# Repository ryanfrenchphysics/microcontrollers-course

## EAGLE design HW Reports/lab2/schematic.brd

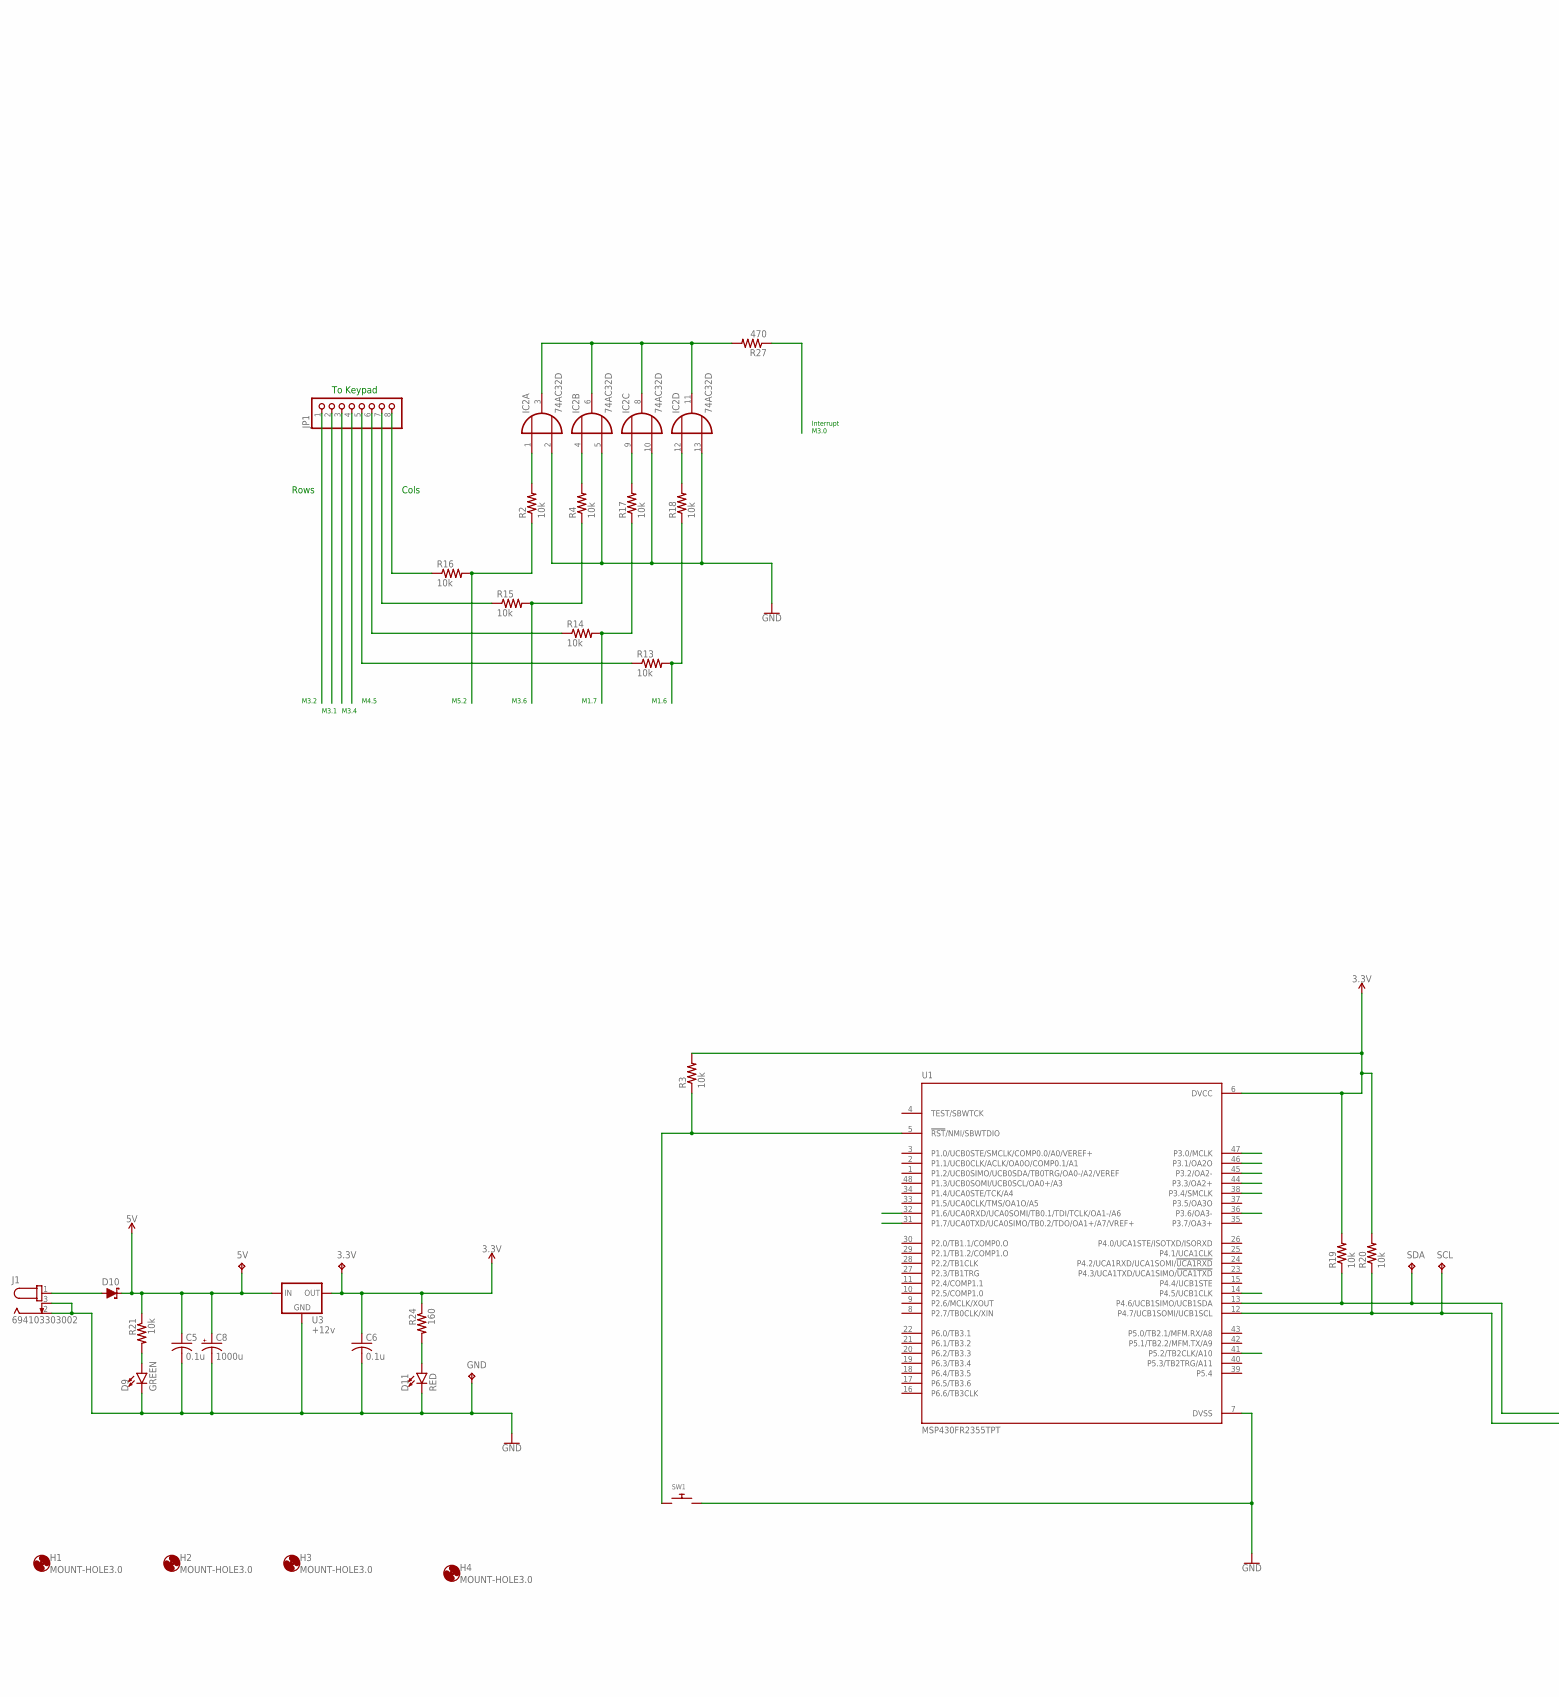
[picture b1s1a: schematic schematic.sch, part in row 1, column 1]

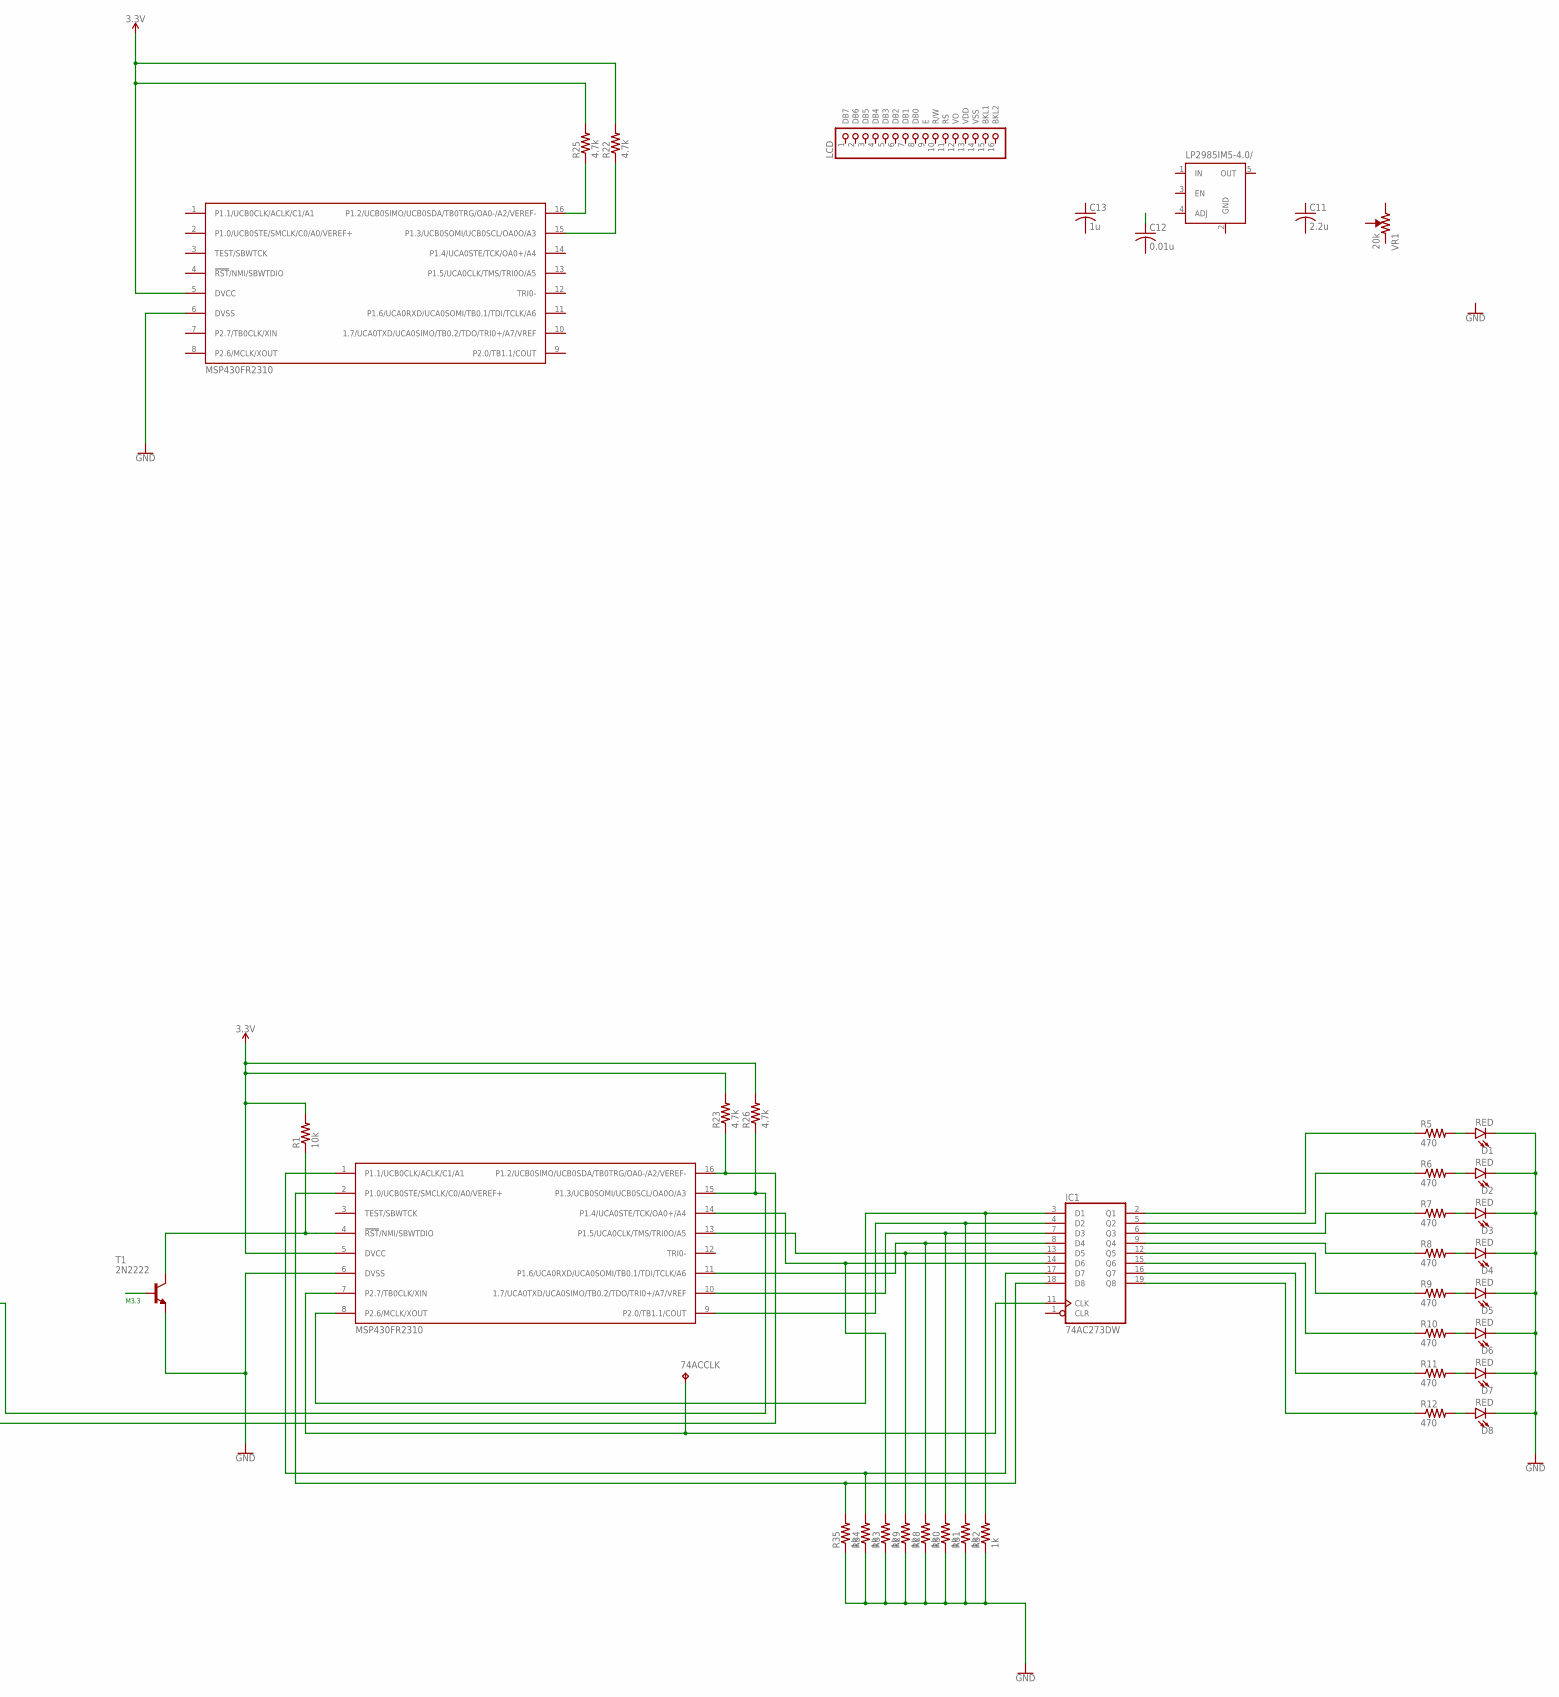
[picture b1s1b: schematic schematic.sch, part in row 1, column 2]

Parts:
3.3V, 5V, 74ACCLK: TPPAD1-17; P1-17
C5, C6: 0.1u; C1206
C8: 1000u; E2,5-6E
C11: 2.2u; C0603
C12: 0.01u; C0603
C13: 1u; C0603
D1, D2, D3, D4, D5, D6, D7, D8, D11: RED; LED-1206
D9: GREEN; LED-1206
D10: DIODE-SCHOTTKY-SS14; SMA-DIODE
GND: TPPAD1-17; P1-17
H1, H2, H3, H4: MOUNT-HOLE3.0; 3,0
IC1: 74AC273DW; SO20W
IC2: 74AC32D; SO14
J1: 694103303002
JP1: PINHD-1X8/90; 1X08/90
LCD: PINHD-1X16; 1X16
LP2985IM5-4.0/: LP2985IM5-4.0/; SOT23-5
R1: 10k; RESC1608X60
R2, R3, R4, R13, R14, R15, R16, R17, R18, R19, R20, R21: 10k; RESC3216X70
R5, R6, R7, R8, R9, R10, R11, R12, R27: 470; RESC3216X70
R22, R23, R25, R26: 4.7k; RESC1608X60
R24: 160; RESC3216X70
R28, R29, R30, R31, R32, R33, R34, R35: 1k; RESC3216X70
SCL: TPPAD1-17; P1-17
SDA: TPPAD1-17; P1-17
SW1: SWITCH_PUSHBUTTONC&K_KSS; BTN_CK_KSS
T1: 2N2222; TO92-EBC-OVAL
U1: MSP430FR2355TPT; QFP50P900X900X160-48N
U3: +12v; TO-252
U$1, U$2: MSP430FR2310; SOP65P640X120-16N
VR1: 20k; TRIMPOT-SMD-3MM-CLOSED

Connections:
5V: 5V.TP, C5.1, C8.+, D10.C, R21.1, U3.1 (IN)
GND: C5.2, C6.2, C8.-, D1.C, D2.C, D3.C, D4.C, D5.C, D6.C, D7.C, D8.C, D9.C, D11.C, GND.TP, IC1.10 (GND), IC2.2 (I1), IC2.5 (I1), IC2.7 (GND), IC2.10 (I1), IC2.13 (I1), J1.2, J1.3, LP2985IM5-4.0/.2 (GND), R28.1, R29.1, R30.1, R31.1, R32.1, R33.1, R34.1, R35.1, SW1.P$2, T1.E, U1.7 (DVSS), U3.3 (GND), U$1.6 (DVSS), U$2.6 (DVSS)
KEY_COL1: R2.1, R16.2, U1.41 (P5.2/TB2CLK/A10)
KEY_COL2: R4.1, R15.2, U1.36 (P3.6/OA3-)
KEY_COL3: R14.2, R17.1, U1.31 (P1.7/UCA0TXD/UCA0SIMO/TB0.2/TDO/OA1+/A7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)
KEY_COL4: R13.2, R18.1, U1.32 (P1.6/UCA0RXD/UCA0SOMI/TB0.1/TDI/TCLK/OA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)
KEY_INT: IC2.3 (O), IC2.6 (O), IC2.8 (O), IC2.11 (O), R27.1, R27.2, U1.47 (P3.0/MCLK)
KEY_ROW1: JP1.1, U1.45 (P3.2/OA2-)
KEY_ROW2: JP1.2, U1.46 (P3.1/OA2O)
KEY_ROW3: JP1.3, U1.38 (P3.4/SMCLK)
KEY_ROW4: JP1.4, U1.14 (P4.5/UCB1CLK)
LED_RST: T1.B, U1.44 (P3.3/OA2+)
unnamed: R25.1, U$2.16 (P1.2/UCB0SIMO/UCB0SDA/TB0TRG/OA0-/A2/VE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)
unnamed: IC1.18 (D8), R35.2, U$1.2 (P1.0/UCB0STE/SMCLK/C0/A0/VEREF+)
unnamed: R3.1, SW1.P$1, U1.5 (!RST!/NMI/SBWTDIO)
unnamed: R1.1, T1.C, U$1.4 (!RST!/NMI/SBWTDIO)
unnamed: D1.A, R5.2
unnamed: D2.A, R6.2
unnamed: D3.A, R7.2
unnamed: D4.A, R8.2
unnamed: D5.A, R9.2
unnamed: D6.A, R10.2
unnamed: D7.A, R11.2
unnamed: D8.A, R12.2
unnamed: IC1.17 (D7), R34.2, U$1.1 (P1.1/UCB0CLK/ACLK/C1/A1)
unnamed: IC1.14 (D6), R33.2, U$1.14 (P1.4/UCA0STE/TCK/OA0+/A4)
unnamed: IC1.13 (D5), R29.2, U$1.13 (P1.5/UCA0CLK/TMS/TRI0O/A5)
unnamed: IC1.3 (D1), R32.2, U$1.8 (P2.6/MCLK/XOUT)
unnamed: 74ACCLK.TP, IC1.11 (CLK), U$1.7 (P2.7/TB0CLK/XIN)
unnamed: IC1.2 (Q1), R5.1
unnamed: IC1.5 (Q2), R6.1
unnamed: D11.A, R24.2
unnamed: IC1.6 (Q3), R7.1
unnamed: IC1.9 (Q4), R8.1
unnamed: IC1.12 (Q5), R9.1
unnamed: IC1.15 (Q6), R10.1
unnamed: IC1.16 (Q7), R11.1
unnamed: IC1.19 (Q8), R12.1
unnamed: IC2.1 (I0), R2.2
unnamed: IC2.4 (I0), R4.2
unnamed: R19.1, R26.1, SDA.TP, U1.13 (P4.6/UCB1SIMO/UCB1SDA), U$1.15 (P1.3/UCB0SOMI/UCB0SCL/OA0O/A3)
unnamed: IC2.9 (I0), R17.2
unnamed: IC2.12 (I0), R18.2
unnamed: JP1.8, R16.1
unnamed: JP1.7, R15.1
unnamed: JP1.6, R14.1
unnamed: JP1.5, R13.1
unnamed: R22.1, U$2.15 (P1.3/UCB0SOMI/UCB0SCL/OA0O/A3)
unnamed: D9.A, R21.2
unnamed: IC1.8 (D4), R28.2, U$1.11 (P1.6/UCA0RXD/UCA0SOMI/TB0.1/TDI/TCLK/A6)
unnamed: IC1.7 (D3), R30.2, U$1.10 (1.7/UCA0TXD/UCA0SIMO/TB0.2/TDO/TRI0+/A7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)
unnamed: IC1.4 (D2), R31.2, U$1.9 (P2.0/TB1.1/COUT)
unnamed: D10.A, J1.1
SCL: R20.1, R23.1, SCL.TP, U1.12 (P4.7/UCB1SOMI/UCB1SCL), U$1.16 (P1.2/UCB0SIMO/UCB0SDA/TB0TRG/OA0-/A2/VE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)
VCC: IC1.20 (VCC), IC2.14 (VCC)
VDD: 3.3V.TP, C6.1, R1.2, R3.2, R19.2, R20.2, R22.2, R23.2, R24.1, R25.2, R26.2, U1.6 (DVCC), U3.2 (OUT), U$1.5 (DVCC), U$2.5 (DVCC)

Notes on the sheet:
To Keypad
Interrupt M3.0
Rows
Cols
M3.2
M3.1
M3.4
M4.5
M5.2
M3.6
M1.7
M1.6
M3.3

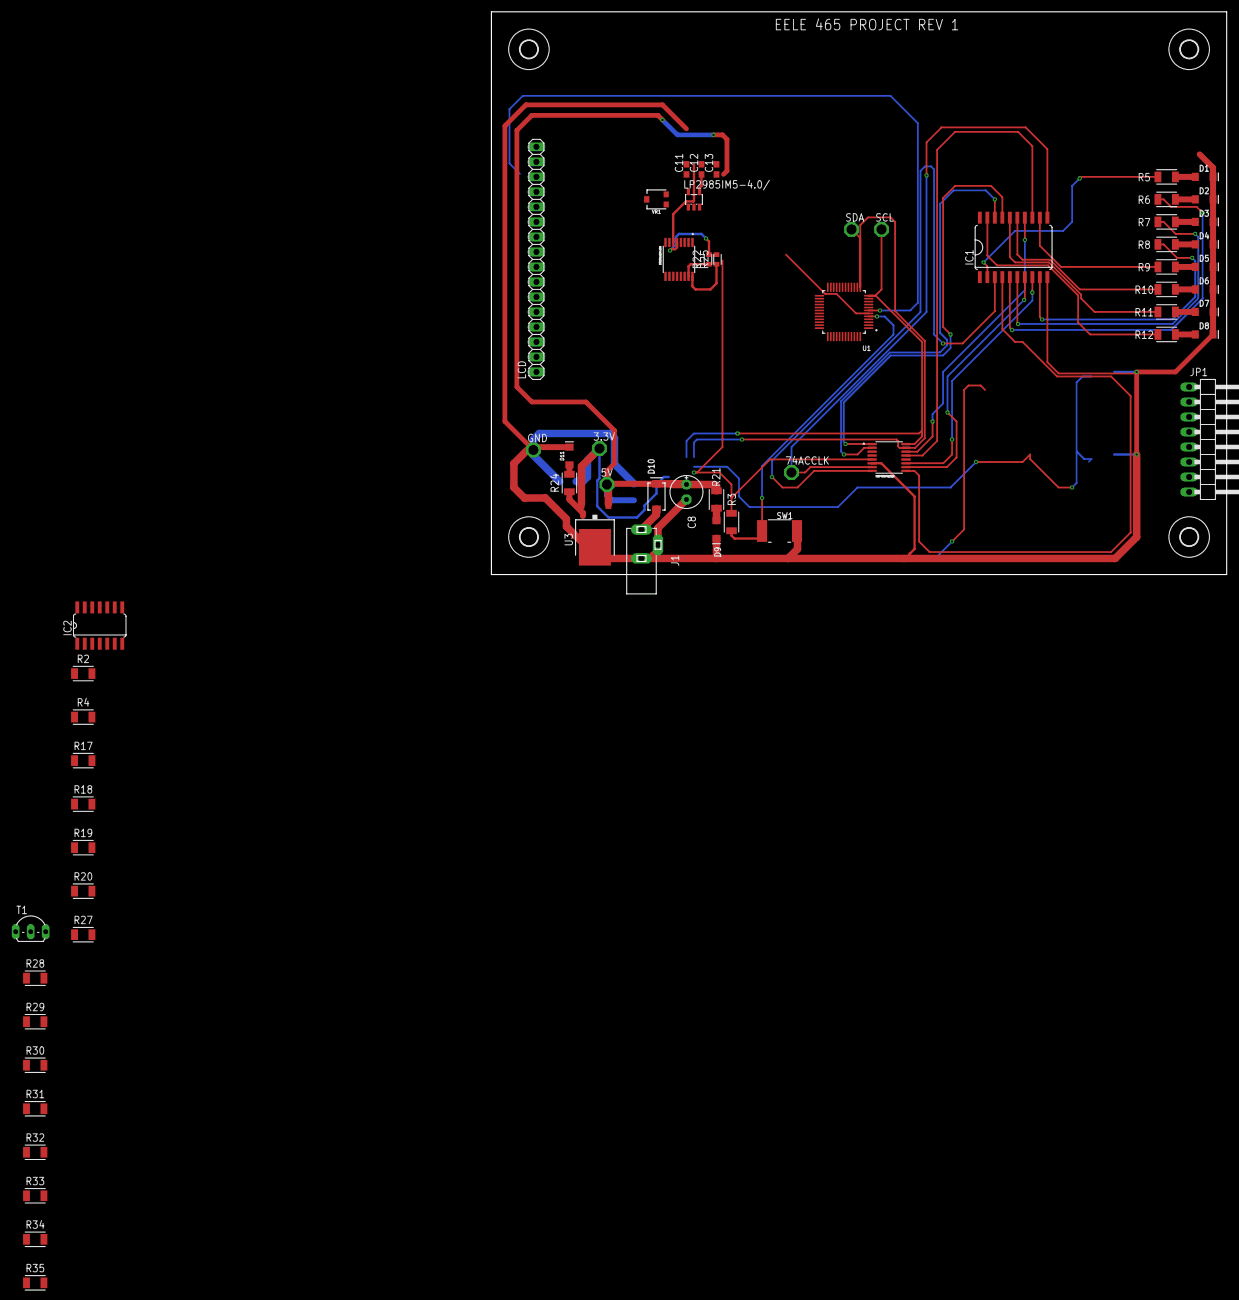
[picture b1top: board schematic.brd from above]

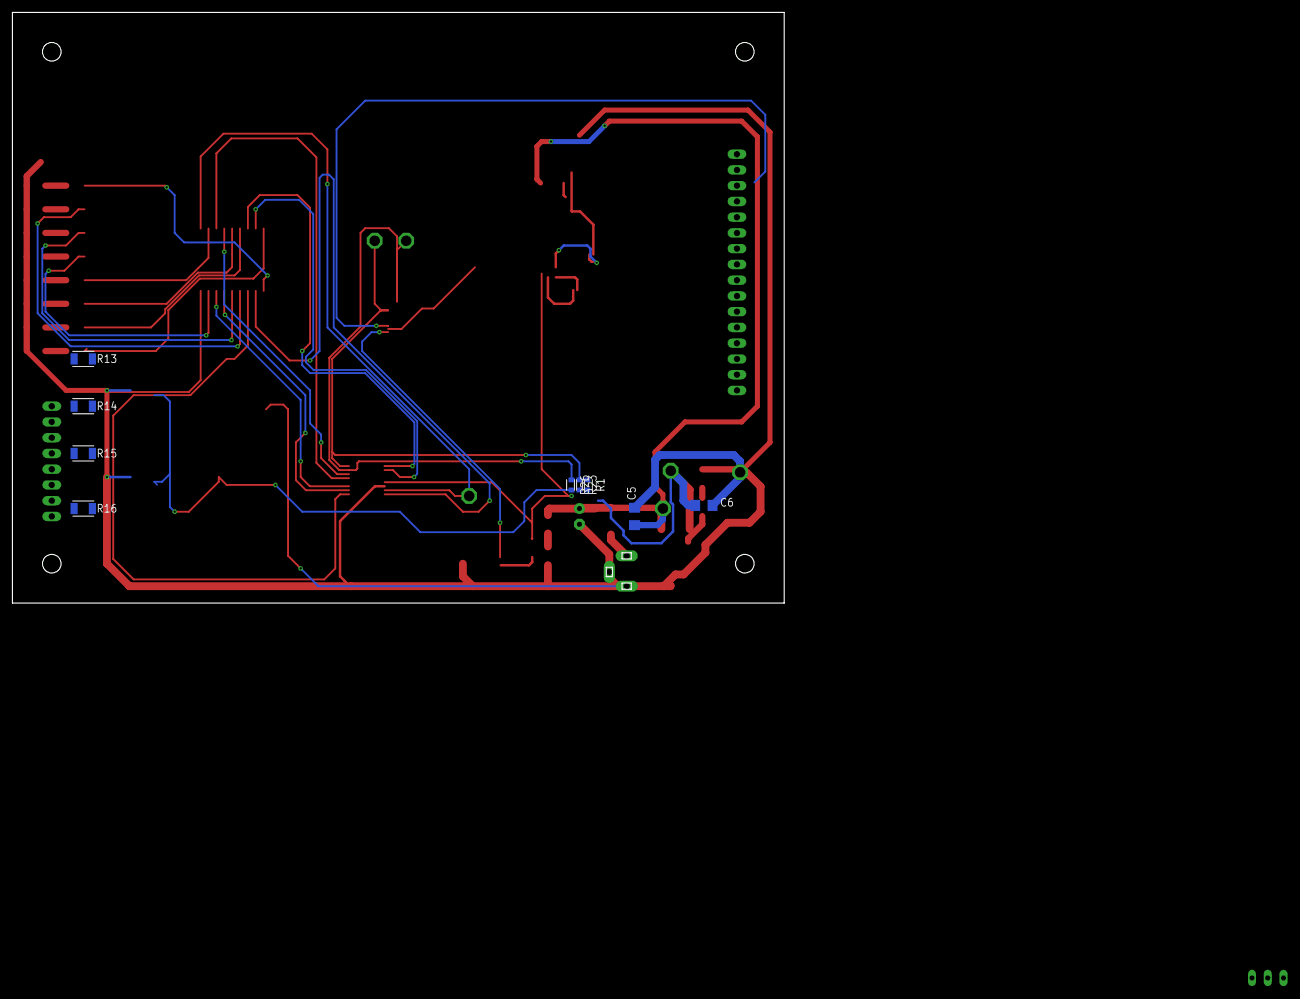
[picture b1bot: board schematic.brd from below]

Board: 2 copper layers, 124.5 x 95.2 mm, 75 parts (9 on the bottom side), 56 nets.

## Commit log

2020-12-01 First commit. Added all the stuff I had on my local machine.
2020-12-01 Removed large MP4 files

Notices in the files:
parts and their libraries:
SparkFun-LED: Licensing: Creative Commons ShareAlike 4.0 International - https://creativecommons.org/licenses/by-sa/4.0
